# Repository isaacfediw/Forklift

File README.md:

# Forklift
This project is a remote controlled electric forklift that I made with a partner for a 4 week course at BCIT  
  
## Electrical Hardware
The electrical hardware for this project consisted of a Rasberry Pi 4, a custom made pcb, two dc motor drivers, and two stepper motor drivers  
The forklift had two modes; automatic and manual. When in manual mode it was controlled via bluetooth with an XBox One controller  
  
## Software
The mechanical design of the forklift was done in Fusion 360. The design files are included in this project in case you're interested  
The forklift was coded on the raspberry pi in c++ using CodeBlocks IDE  
  
## Pictures

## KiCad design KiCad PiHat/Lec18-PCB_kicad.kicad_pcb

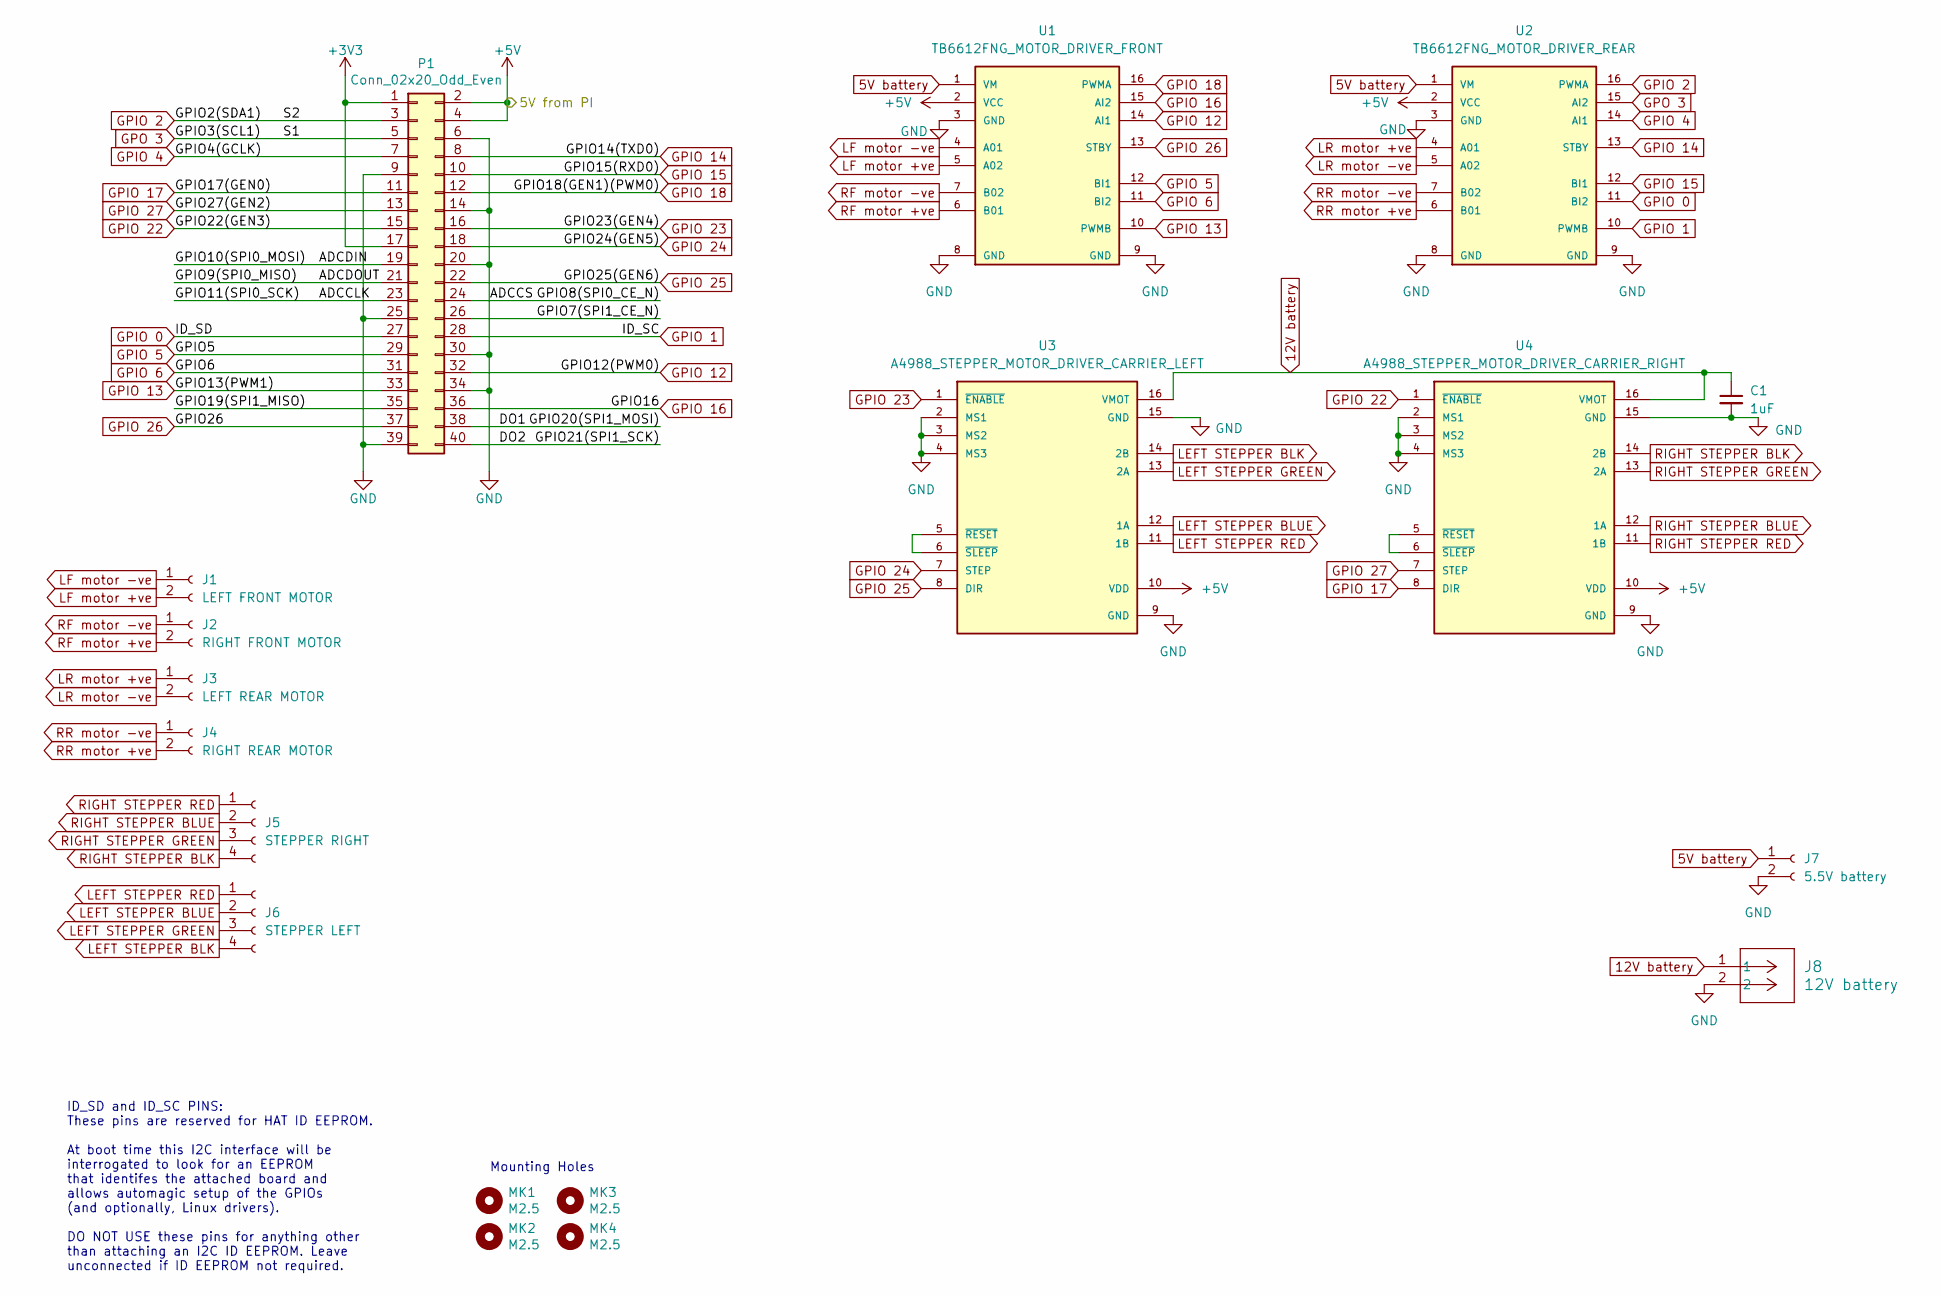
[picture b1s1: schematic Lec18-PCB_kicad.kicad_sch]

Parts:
C1: 1uF; C_Radial_D4.0mm_H7.0mm_P1.50mm
J1: LEFT FRONT MOTOR; PinSocket_1x02_P2.54mm_Vertical
J2: RIGHT FRONT MOTOR; PinSocket_1x02_P2.54mm_Vertical
J3: LEFT REAR MOTOR; PinSocket_1x02_P2.54mm_Vertical
J4: RIGHT REAR MOTOR; PinSocket_1x02_P2.54mm_Vertical
J5: STEPPER RIGHT; PinSocket_1x04_P2.54mm_Vertical
J6: STEPPER LEFT; PinSocket_1x04_P2.54mm_Vertical
J7: 5.5V battery; PinSocket_1x02_P2.54mm_Vertical
J8: 12V battery; CONN_B2P-VH_JST
MK1, MK2, MK3, MK4: M2.5; MountingHole_2.7mm_M2.5
P1: Conn_02x20_Odd_Even; PinSocket_2x20_P2.54mm_Vertical
U1: TB6612FNG_MOTOR_DRIVER_FRONT; MODULE_ROB-14450; PARTREV 11-13-17
U2: TB6612FNG_MOTOR_DRIVER_REAR; MODULE_ROB-14450; PARTREV 11-13-17
U3: A4988_STEPPER_MOTOR_DRIVER_CARRIER_LEFT; MODULE_A4988_STEPPER_MOTOR_DRIVER_CARRIER
U4: A4988_STEPPER_MOTOR_DRIVER_CARRIER_RIGHT; MODULE_A4988_STEPPER_MOTOR_DRIVER_CARRIER

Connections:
5V battery: J7.1, U1.1 (VM), U2.1 (VM)
12V battery: C1.1, J8.1, U3.16 (VMOT), U4.16 (VMOT)
+3V3: P1.1, P1.17
+5V: P1.2, P1.4, U1.2 (VCC), U2.2 (VCC), U3.10 (VDD), U4.10 (VDD)
/ADCCLK: P1.23
/ADCDIN: P1.19
/ADCDOUT: P1.21
/DO1: P1.38
/DO2: P1.40
/GPIO7(SPI1_CE_N): P1.26
/GPIO19(SPI1_MISO): P1.35
GPIO 0: P1.27, U2.11 (BI2)
GPIO 1: P1.28, U2.10 (PWMB)
GPIO 2: P1.3, U2.16 (PWMA)
GPIO 4: P1.7, U2.14 (AI1)
GPIO 5: P1.29, U1.12 (BI1)
GPIO 6: P1.31, U1.11 (BI2)
GPIO 12: P1.32, U1.14 (AI1)
GPIO 13: P1.33, U1.10 (PWMB)
GPIO 14: P1.8, U2.13 (STBY)
GPIO 15: P1.10, U2.12 (BI1)
GPIO 16: P1.36, U1.15 (AI2)
GPIO 17: P1.11, U4.8 (DIR)
GPIO 18: P1.12, U1.16 (PWMA)
GPIO 22: P1.15, U4.1 (~ENABLE)
GPIO 23: P1.16, U3.1 (~ENABLE)
GPIO 24: P1.18, U3.7 (STEP)
GPIO 25: P1.22, U3.8 (DIR)
GPIO 26: P1.37, U1.13 (STBY)
GPIO 27: P1.13, U4.7 (STEP)
GPO 3: P1.5, U2.15 (AI2)
LEFT STEPPER BLK: J6.4, U3.14 (2B)
LEFT STEPPER BLUE: J6.2, U3.12 (1A)
LEFT STEPPER GREEN: J6.3, U3.13 (2A)
LEFT STEPPER RED: J6.1, U3.11 (1B)
LF motor +ve: J1.2, U1.5 (A02)
LF motor -ve: J1.1, U1.4 (A01)
LR motor +ve: J3.1, U2.4 (A01)
LR motor -ve: J3.2, U2.5 (A02)
unnamed: U3.5 (~RESET), U3.6 (~SLEEP)
unnamed: U4.5 (~RESET), U4.6 (~SLEEP)
RF motor +ve: J2.2, U1.6 (B01)
RF motor -ve: J2.1, U1.7 (B02)
RIGHT STEPPER BLK: J5.4, U4.14 (2B)
RIGHT STEPPER BLUE: J5.2, U4.12 (1A)
RIGHT STEPPER GREEN: J5.3, U4.13 (2A)
RIGHT STEPPER RED: J5.1, U4.11 (1B)
RR motor +ve: J4.2, U2.6 (B01)
RR motor -ve: J4.1, U2.7 (B02)

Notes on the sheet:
ID_SD and ID_SC PINS: These pins are reserved for HAT ID EEPROM. At boot time this I2C interface will be interrogated to look for an EEPROM that identifes the attached board and allows automagic setup of the GPIOs (and optionally, Linux drivers). DO NOT USE these pins for anything other than attach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
Mounting Holes

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
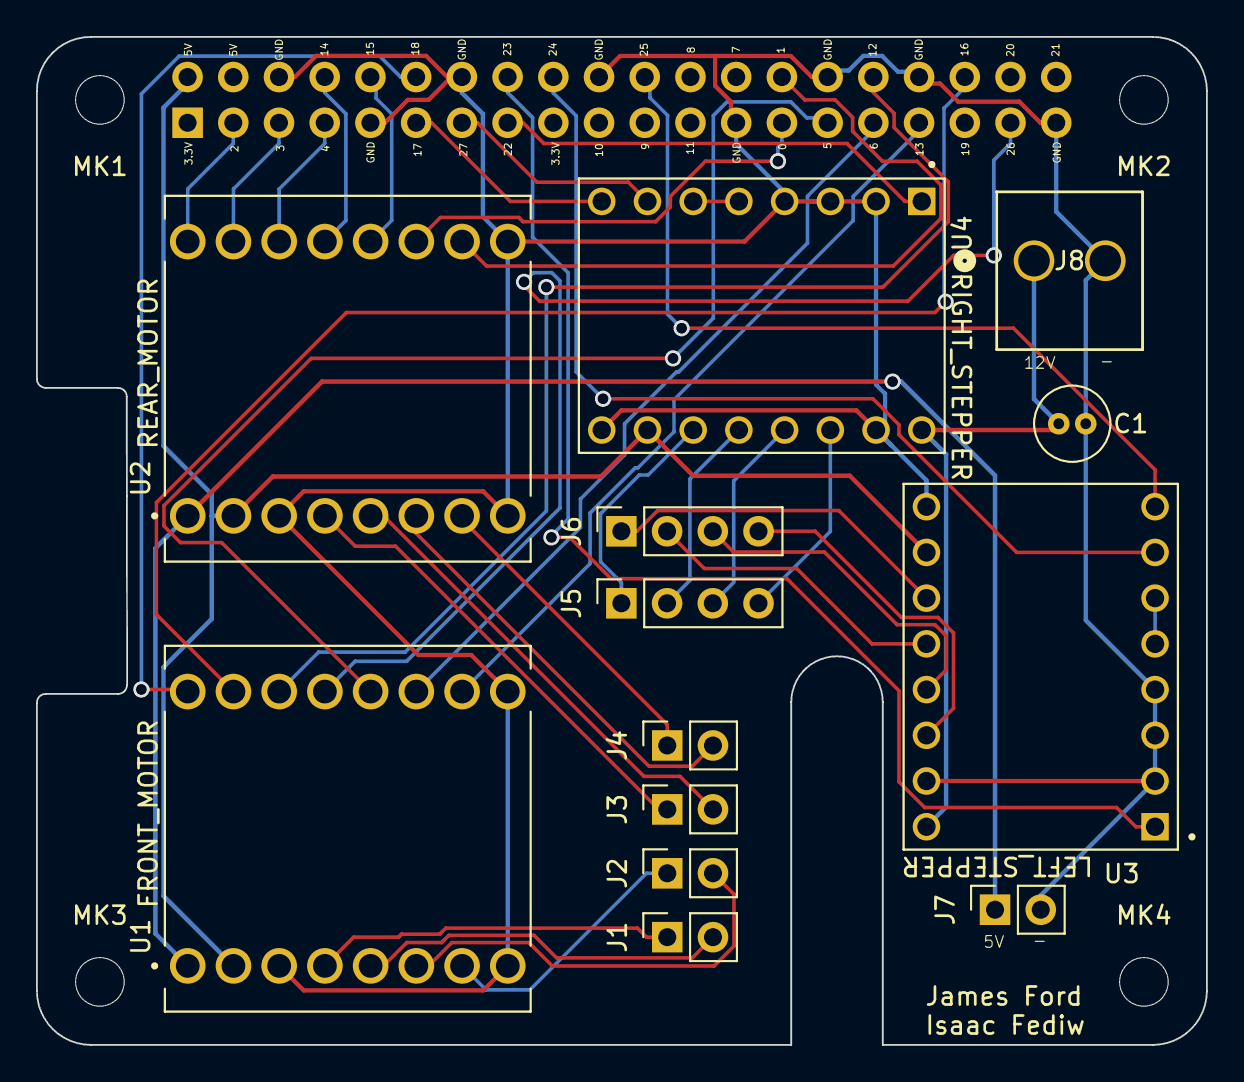
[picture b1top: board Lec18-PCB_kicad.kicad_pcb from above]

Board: 2 copper layers, 65.0 x 56.0 mm, 18 parts (1 on the bottom side), 43 nets.

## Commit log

2026-01-15 Enhance README with project details and images
    Added sections for electrical hardware, software, and pictures.
2026-01-15 Update README with control modes details
    Added information about the forklift's control modes.
2026-01-15 Add link to GitHub assets in Autonomous-Demo.md
2026-01-15 Rename Autonomous-Demo.md to Autonomous Demo.md
